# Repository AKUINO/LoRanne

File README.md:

# Long Range (LoRa) Radio Sensors for AKUINO
After connecting wired 17 sensors to a single AKUINO, we were convinced that wireless is very useful...

With the advent of LoRA transmission technology which ensures a really good indoor range, with the availability of ready to use modules like AdaFruit Feather M0 able to transmit data for years with simple batteries, we are convinced that a very performant solution can be created.
## Hardware

Transmitters (working on batteries, collecting and transmitting sensors data, sleeping most of the time) are explained further here: https://github.com/AKUINO/RadioSensor/tree/master/transmitter

Receiver(s) (powered, collecting transmitted data, archiving it locally, transmitting on Internet, never sleeping) is explained further here: https://github.com/AKUINO/RadioSensor/tree/master/receiver

General design considerations:

* Transmitters: Arduino MKR WAN 1300 https://store.arduino.cc/mkr-wan-1300 (was AdaFruit Feather M0: https://www.adafruit.com/product/3179 but AdaFruit products are rarely certified "CE")
* Receiver: for transmitters, we are also switching to an integrated "CE" marked product, M5STACK Code Module: https://m5stack.com/collections/m5-core
* 1-Wire sensors have the advantage of being self-identified, "hot-pluggable" and could be connected to one sensor node or another: https://www.maximintegrated.com/en/app-notes/index.mvp/id/4206
  * Serial adapter for 1-Wire gives better reliability than bit-banging (e.g. https://www.mikroe.com/uart-1-wire-click ) but requires 5V. As most 1-Wire devices are happy (but sometimes slower) at 3.3V, fewer devices not too far away will make bit-banging possible.
  * Thermocron (IButton: https://be.farnell.com/fr-BE/c/semiconducteurs-circuits-integres/memoires/accessoires-iboutons/iboutons ) can receive a "mission" and record temperature OFF-LINE for very long period of time: they can be used to ensure cold-chain continuity during transportation. They can even be programmed by a remote radio module: http://arduinofun.blogspot.com/2010/04/arduino-ibutton-data-logger-programmer.html . We have programmed data download and missioning of Thermocron by ELSA
  * Mains Switch: https://www.axiris.eu/en/index.php/1-wire/1-wire-mains-switch
* I2C sensors are often working at 3.3V and 5V. Short wires though (20 cm max: should be in the same box than the radio module)
  * I2C CO2+temperature+humidity: https://befr.rs-online.com/web/p/products/1720552/?grossPrice=Y&cm_mmc=BE-PLA-DS3A-_-google-_-PLA_BE_NL_Semiconductors-_-Sensor_Ics|Temperature_And_Humidity_Sensors-_-PRODUCT_GROUP&matchtype=&pla-544508151584&gclid=Cj0KCQiAzKnjBRDPARIsAKxfTRA_NGOGs_dE9fBuCA61ZyCIf1GovlkXcqFPyUBE3JYgCDP7rXKEHxUaAuaREALw_wcB&gclsrc=aw.ds
  * I2C Temperature and/or humidity: https://befr.rs-online.com/web/c/semiconductors/sensor-ics/temperature-sensors-humidity-sensors/?searchTerm=i2c%20sensor&applied-dimensions=4293448979,4294510394,4294490065,4294505396,4294510395,4294510203,4294356324,4294821500 and also https://www.tindie.com/products/akdracom/temperature-humidity-sensor-probe-precision-ic/
  * Grove Wiring standard is often used and is similar to QWIIC from Sparkfun: https://www.sparkfun.com/qwiic (Grove as a normal pitch connector, Sparkfun is smaller; Beware: AdaFruit standard is different!):
  1. Yellow - SCL
  1. White - SDA (Blue for QWIIC)
  1. Red - VCC on all Grove Connectors
  1. Black - GND on all Grove Connectors
  M5Stack Core is equipped with a Grove I2C connector.
* Lithium Battery: https://shop.mchobby.be/accu-et-regulateur/746-accu-lipo-37v-4400mah-3232100007468.html , https://be.farnell.com/fr-BE/mikroelektronika/mikroe-1120/batterie-lithium-polymer-3-7v/dp/2786900 , https://www.onlylipo.com/21-1s-37-volts-1-element
* Enclosures:
  * We selected KRADEX 64mm x 88mm x 42mm: https://www.tme.eu/fr/details/z-56jh-abs/boitiers-universels/kradex/z56jh-abs/ looking like CEL-MAR 1-Wire boxes that we also use.
  * 8 x 8cm, 5cm deep: many electrical junction boxes
  * 10 x 10cm, 6cm deep: http://be.farnell.com/fr-BE/fibox/pcm-95-60-g/coffret-boite-polycarbonate-gris/dp/2473443

## Software
* RadioHead libraries: http://www.airspayce.com/mikem/arduino/RadioHead/index.html Be sure to use the latest version (1.89)
  * for LoRa: http://www.airspayce.com/mikem/arduino/RadioHead/classRH__RF95.html

* 1-wire:
  * Host driver: https://www.maximintegrated.com/en/products/ibutton/software/1wire/wirekit.cfm
  * Recommended by Adafruit: https://www.pjrc.com/teensy/td_libs_OneWire.html
  * Slave device emulation library: https://github.com/orgua/OneWireHub (in case we want to connect to host through 1-wire)

* AdaFruit Feather M0, Arduino IDE SAMD support: https://learn.adafruit.com/adafruit-feather-m0-basic-proto/using-with-arduino-ide

## LoRa
* Allowed duty cycle and power in different 868MHz bands: https://www.disk91.com/2017/technology/internet-of-things-technology/all-what-you-need-to-know-about-regulation-on-rf-868mhz-for-lpwan/ From this document, the best local bandwidth could be 869,3 to 869,4 limited to 10mW but with no duty cycle constraint.
  * We measured 7 packets of 37 characters per seconds when testing this radio band.  
* 433 MHz may not be allowed in production within Europe: the project may have to be announced as "RFID" if we stick to those frequencies
  * In this band, we reached 540 meters in a corn field (emmiter and receiver at the corn height; single wire antenna)
* Calculator of Allowed duty cycle for different LoRa configurations: https://docs.google.com/spreadsheets/d/1COg2J1at6j8meehTtvfj5TIiM8pbj4SvKf7sa-Oq5fU/edit#gid=1628588258
## Sensors
Each node can receive many kind of sensors and its firmware can be adapted for each situation: the USB programming port of the node can be used to either change the firmware or to access a terminal console and change parameters.

An important information is battery voltage: its value will always be read and transmitted (register 1).

### I2C
I2C runs on 5V but also on 3.3V (not all sensors but most). Wires must be kept very short (20cm max, less is better).

The commands are different for each type of sensors: the bus cannot be really "auto discovered" like with 1-Wire (see below). The only possible thing is to associate I2C addresses with possible devices...

### 1-Wire
1-Wire ensures auto-configuration (devices can be "discovered" on the bus). Each 1-Wire device have a unique 64 bits address which can be auto-discovered by polling the 1-Wire bus (owdir on Linux, the equivalent will have to be programmed using libraries like https://www.pjrc.com/teensy/td_libs_OneWire.html ). The 8 first bits of this address indicates a generic device type which will have to be known by the firmware to adapt itself to the characteristics of each device type (e.g. number of values, polling protocol, parasitic powering...). The 8 last bits are a CRC8 checksum of the 7 previous bytes. It must be verified after each transmission (wire or radio) to ensure data integrity.

List of existing device types: http://owfs.org/index.php?page=family-code-list

The device types that we really need to support at first are:
* 26 for the DS2438 Battery Monitor (used as an ADC for various types of sensors like RH, CO2...)
* 28 for the DS18B20 Temperature Sensor; a library directly supporting this device seems to exist: https://github.com/milesburton/Arduino-Temperature-Control-Library This may be the best way to start supporting some sensors...
* 01 for the DS1990 simulated by RFID badge reader

A central directory of 1-Wire devices will be kept locally but also in the Receiver (and in ELSA application).

Every minutes or 5 (or any delay set in configuration), the node will transmit the raw data (no scaling) read for the different sensors. The allocation table will be transmitted every hour (or delay set in configuration) or on request by the central node (after detection of a checksum mismatch with the allocation table).

Data will be processed by the sensor node to transmit only specific JSON data values like "temperature" and not all registers of the device.

## Messages
* Encryption: http://www.airspayce.com/mikem/arduino/RadioHead/classRHEncryptedDriver.html#details
* Header with:
  * "FROM" (for sensors, the id of current node; for central node, id to distinguish the right central node)
	  * encoded on one byte
  * "TO" (for sensors, id of their central node; for central node, 255 for broadcast or id of a specific node to be queried)
	  * encoded on one byte
  * "ID", for a given "FROM"-"TO"-"FLAGS" combination, is a sequence ID of the message (overflow at 255): it allows the receiver to detect it has missed messages (and take action to correct this situation if needed).
  * "FLAGS" specifies the type of message: sensors data vs actuators (registers) setting; retransmission request (messages missed by receiver, the receiver signals which ID are missing); devices table to identify connected 1-Wire or I2C devices (from sensor node to central); relaying (MESH protocol, to be designed)
  * Sensors Data message: see below

## Sensors Data Messages
There are many encoding formats (see bottom of https://github.com/AKUINO/JBCDIC/blob/master/README.md ).

Please look at our proposal, the project AKUINO/JBCDIC: https://github.com/AKUINO/JBCDIC !

## Protocol
* A potential source of inspiration: https://github.com/fredilarsen/ModuleInterface/blob/master/documentation/Protocol.md
* A remote module (sensors) is sleeping most of the time (does not listen to radio) and awakens from time to time (around 3 minutes) to collect data and send it to the central module.
* A central module is listening all the time and sends actuators settings (or retransmission requests) only just after receiving sensors data from a remote module.
* The sender listen to the air and wait for silence (random delay) to avoid collision (this is done by the radio chip SX127x but needs to be configured. Looking at RadioHead library source code, it can be done: https://github.com/adafruit/RadioHead/blob/master/RH_RF95.h ). This is called LBT (Listen Before Talk).
* The message is sent using RadioHead library (encrypted but no ACK required).
* For remote module, the sender keeps listening for eventual input messages from the destination (actuators settings, sensors data retransmission requests) during a short period of time.
* If a remote module notices that some actuators settings are missing, it requests their retransmission.
* Sensor nodes send their 1-Wire / I2C Allocation table either periodically (about an hour), either when some connection changes is detected or whenever a request for it is received from the central node
* Retransmission request: timestamp + pairs of bytes for each ID intervals ("begin ID"-"end ID") that needs to be (re)transmitted. Overflow may occur (increment of 255 is 0) and "end ID" can be lower than "begin ID".
* Retransmission: message with exactly the same Header (TO, FROM, ID, FLAGS) and Payload than the one transmitted before

All nodes will be responsible to keep a buffer of the last messages (254 last messages for sensors and 254 last messages for actuators) they sent.

Redundancy of central module is possible: the two modules then share the same ID. A central module may not have received a package and therefore ask to retransmit a message well received by the other module: redundant transmissions are therefore discarded based on ID+timestamp.

## Configuration
We will use a serial terminal (USB) to set the configuration parameters (ANSI character codes for colors). We have the necessary code in C++ for PIC32. The configuration will have to assign a key (0 to 31) to the physically connected ports:
* Digital inputs: for a 1st version, we will statically map some GPIO as 0/1 ports
* Analog inputs (12 bits): for a 1st version, we will statically map some ADC inputs including at least the battery level and 2 ADC lines
* Digital outputs (PWM, pull-up, delays) to be SET (based on messages received from central): for a 1st version, we will statically map some PWM lines with basic local configuration attributes.
* 1-Wire (multiple sensors: 1-Wire addresses AUTOMATICALLY mapped to different keys but a selection of registries may have to be done based on the device type. ABANDONED for now due to lack of 5V...)
* Serial link (not for a 1st version except if a precise need arise)
* Campbell SDI (not for a 1st version except if a precise need arise)
* I2C device initialization command and register read: this is not well standardized but we will try to orthogonalize the possibilities.
A basic polling cycle (e.g. 3 minutes) has to be set. Each key can be obtained either at each poll or at a configured multiple.

## References
* The Ten Commandments of Wireless Communications: http://www.bb-elec.com/Learning-Center/All-White-Papers/Wireless-Cellular/10-Commandments-of-Wireless-Communications/10_Commandments_Wireless_WP033_R2-1112.pdf
* Detailed RadioHead interface: https://github.com/adafruit/RadioHead/blob/master/RH_RF95.h
* The standard pinout of Feather M0 is: https://cdn-learn.adafruit.com/assets/assets/000/046/244/original/adafruit_products_Feather_M0_Basic_Proto_v2.2-1.png?1504885373
* Similar project but for very long range: http://cpham.perso.univ-pau.fr/LORA/WAZIUP/FAQ.pdf
  * http://cpham.perso.univ-pau.fr/LORA/WAZIUP/SUTS-demo-slides.pdf
* CayenneLPP: https://mydevices.com/cayenne/docs/lora/#lora-cayenne-low-power-payload
* PJON, an alternative transmission protocol: https://github.com/fredilarsen/ModuleInterface/blob/master/documentation/Protocol.md
* PlugAndPlay mechanism for small IoT networks using "off the shelf" sensors: http://pitkaaho.net/varasto/2013_IJSNet.pdf
* MainFlux does not seems to be locking anything (to double check!) and is involved in FIWARE and is very near of a good gateway for ELSA: https://www.mainflux.com/index.html
* LORD-MicroStrain is locking by the hardware : https://github.com/LORD-MicroStrain/
* UbiWorX is locking by the platform: https://ubiworx.com/documentation/introduction/introduction.html
* W3C API: https://w3c.github.io/sensors/

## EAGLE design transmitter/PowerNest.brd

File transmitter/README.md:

# TRANSMITTER
In a "star" network there are modules collecting data in different places (transmitters) and one or two "data sinks" (receivers, gateways) that route the data to the data management application.

The transmitters must be as autonomous as possible (minimal configuration, automatic adaptation to new sensors put in place, agnostic about the data: it will be managed by the application, not the transmitter).

They include:
* power management: sensors are powered only when needed, battery power is saved as much as possible
* radio bandwidth management: radio transmission is minimized and assumed "dangerous": if it fails, data is kept up to the moment transmission can resume.

The configuration needed is minimal:
* a Network ID is provided once for all and needs a special boot-up sequence and password to be changed.
* a Network access key and a unique Module ID must be set. They remain normally unchanged. Another password protects those parameters.

The peripherals are automatically detected (1-Wire, I2C). Some may have to be configured (Analog or serial inputs). This is done through a wizard (sequence of questions with current answers provided by defaults).

Radio messages are buffered and exchanged in compressed URL format (see project [JBCDIC](https://github.com/AKUINO/JBCDIC/blob/master/README.md), aimed at compressiong JSON, used to compress URLs).

The transmitter is currently based on the Adafruit Feather M0 with a LoRa transmitter (https://www.adafruit.com/product/3178) but next version will be based on Arduino MKR WAN 1300. We add an underlying board to ease connections to sensors and to selectively power them. The following table explains the pinout:

Connector|Code|Data Pin|Power Activation Pin|Remark
---------|----|--------|--------------------|------
J1-1|g|||GND
J1-2|T|TX (15)|A3 (8)|Serial TX, 10k pull-up
J1-3|R|RX (14)||Serial RX
J1-4|v||A3 (8)|Switched and limited Vcc (see below)
J1-5|g|||GND
J1-6|C|SCL (18)|D11 (23)|I2C clock, 5k pull-up
J1-7|D|SDA (17)|D11 (23)|I2C data, 5k pull-up
J1-8|v||D11 (23)|Switched and limited Vcc (see below)
J1-9|g|||GND
J1-10|O|D13 (25)||LED: Switched Vcc but limited (see below) and 100 ohm
J1-11|I|A0 (5)||Button switch; Analog input protected and filtered for 50Hz
J1-12|v|||Unswitched Vcc limited by 100 ohm
J2-1|g|||GND
J2-2|1|A1 (6)||Analog input protected and filtered for 50Hz
J2-3|v||A4 (9)|Switched and limited Vcc (see below)
J2-4|g|||GND
J2-5|2|A2 (7)||Analog input protected and filtered for 50Hz
J2-6|v||A5 (10)|Switched and limited Vcc (see below)
J2-7|g|||GND
J2-8|W|D5 (19)|D12 (24)|1-Wire bus, 5k pull-up
J2-9|v||D12 (24)|Switched and limited Vcc (see below)
J2-10|10|D10 (22)||Switched and limited Vcc (see below)
J2-11|6|D6 (20)||Switched and limited Vcc (see below)
J2-12|v7||D12 (24)|Switched 7 volts to power RFID/NFC reader (small DC/DC converter from D12)

Distributed power is switched by a TBD62783APG DMOS transistor array (clamping diode included), limited by a 300ma temporary fuse, a 18µH inductance and sustained by a 3µF capacitor.

Detailed Eagle schema and board definition are in this directory.

## Data transmitted

Data is encoded as an URL using JBCDIC ( https://github.com/AKUINO/JBCDIC ). A message is made of only one (for now) session of measures up to the LoRa maximum size (53 bytes in our case).

One measurements session is a URL (in the future: a JSON object) with the following properties:

Property|Connection|Pin|Description
--------|----------|---|-----------
H0|||Seconds ellapsed since module startup. H0 is replaced by H with the correct time by the receiver before resending to the Web application
H|||Seconds since 01/01/2019 (if time was broadcasted by receiver ("data sink") and synchronized with transmitter)
N|||Network Identification number: Not transmitted but added by the receiver before resending to the Web application
M|||Radio Module Identification number: Not transmitted but added by the receiver before resending to the Web application
R|||RSSI for this message: Not transmitted but added by the receiver before resending to the Web application
A0|J1-11|A0|Button pressed? Not transmitted if 0
A1|J2-2|A1|Analog input 1. Not transmitted if 0
A2|J2-5|A2|Analog input 2. Not transmitted if 0
B||A6|Battery voltage
B5||A7|USB voltage (if present). Usually 5 volts if connected
B9|||Last RSSI of messages broadcasted by Receiver (decimal)
C|J1-3|RX|Serial data received (string)
Dnnn|J2-8|D5|Value (or array of values or object with different properties) obtained from 1-Wire device at address "nnn..." (decimal)
G|J2-8|D5|Last badge read by RFID reader (encoded in decimal). Not transmitted if none
G0|J1-10|D13|Button LED on? Not transmitted if not
G1|J2-10|D10|Yellow LED of RFID reader is on? Not transmitted if not
G2|J2-11|D6|Red LED of RFID reader is on? Not transmitted if not
Innn|J1-7|I2C|Value (or array of values or object with different properties) obtained from I2C device at address "nnn" (decimal)

### Data transmission example

Before compression to 4 bits per character:
`{H0+3602A0+1B+3-12B9-78D159300978176+27-2I68[+27-5+40-5]}`
which means:
* `H0+3602` : 3602 seconds elapsed since starting the radio module
* `A0+1` : Button is pressed
* `B+3-12` : Battery is 3.12V
* `B9-78` : Last RSSI was -78 (in decimal)
* `D159300978176+27-2` : the temperature sensor address is 0x2517140600 (not including the leading 0x28 indicating its type and the trailing byte providing an CRC) and its temperature is 27.2°C
* `I68[+27-5+40-5]` : the I2C device at address 0x44 (usually an SHT31 sensor) provides two values: 27.5°C and 40.5% rH

The receiver will receive this data and retransmit it to the Internet application in standard JSON and adding network/module identification:

~~~~
  [ { H:(date/time in seconds elapsed since 1/1/1970 as in UNIX),
     N:1,   (network id)
     M:3,   (module id)
     R:-77,   (RSSI of transmitted message)
     A0:1,     
     B:3.12,    
     B9:-78,    
     D159300978176:27.2,    
     I68:[27.5,40.5]   
    } 
  ]
~~~~

## Software
* Radiohead library for encrypted Lora transmissions
* Protohead for simultaneous execution of data collection and radio transmission
* Periodical wake-ups for collection of sensors values and LoRa transmission (Listen before talk, random delay)
* USB Serial port for the configuration wizard
* JBCDIC for data compression
* FIFO Round Robin Buffer for unacknowledged transmitted data
* Watchdog on button for immediate wakeup, NFC/RFID scan and immediate transmission of status data (including the "button pressed" indication)

## Extensions
* To control equipement in adverse electrical environments, insulation of 1-Wire bus may be useful:  http://www.ti.com/lit/ds/symlink/iso1540.pdf

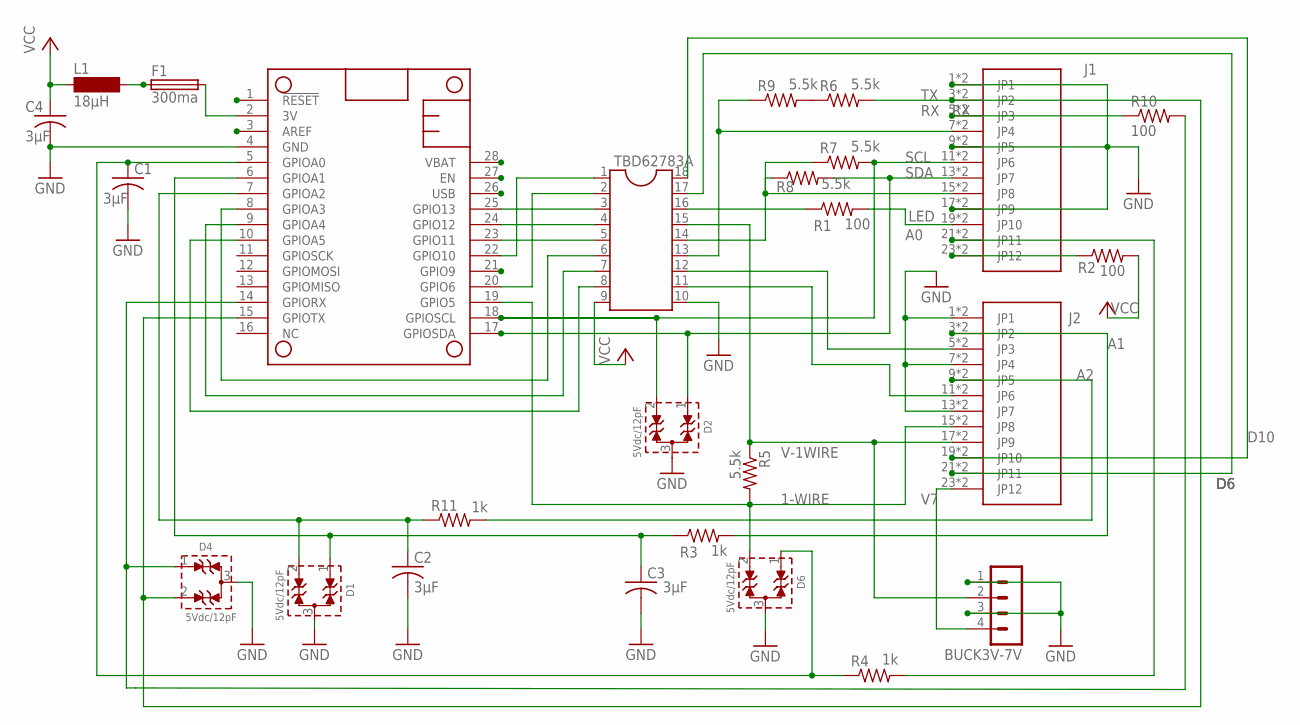
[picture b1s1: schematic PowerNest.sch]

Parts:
BUCK3V-7V: MA04-1
C1, C2, C3, C4: 3µF; C1206K
D1, D2, D4, D6: 5Vdc/12pF; WE-TVS_SOT23-3L
F1: 300ma; TE5
FEATHER: FEATHERWING_NODIM; FEATHERWING_DIM
J1, J2: MC000008B; CONNECTED
L1: 18µH; BS11
R1, R2, R10: 100; R1206
R3, R4, R11: 1k; R1206
R5, R6, R7, R8, R9: 5.5k; R1206
TBD62783A: DIL18S; SOCKET-18

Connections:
1-WIRE: D6.2 (I/O2), FEATHER.19 (GPIO5), J2.15 (JP8), J2.16 (JP8), R5.2
3V: F1.2, FEATHER.2 (3V)
A0: J1.21 (JP11), J1.22 (JP11), R4.2
A1: J2.3 (JP2), J2.4 (JP2), R3.2
A2: J2.9 (JP5), J2.10 (JP5), R11.2
D6: J2.21 (JP11), J2.22 (JP11), TBD62783A.17
D10: J2.19 (JP10), J2.20 (JP10), TBD62783A.18
GND: BUCK3V-7V.1, BUCK3V-7V.3, C1.2, C2.2, C3.2, C4.2, D1.3 (GND), D2.3 (GND), D4.3 (GND), D6.3 (GND), FEATHER.4 (GND), J1.1 (JP1), J1.2 (JP1), J1.9 (JP5), J1.10 (JP5), J1.17 (JP9), J1.18 (JP9), J2.1 (JP1), J2.2 (JP1), J2.7 (JP4), J2.8 (JP4), J2.13 (JP7), J2.14 (JP7), TBD62783A.10
LED: J1.19 (JP10), J1.20 (JP10), R1.2
unnamed: FEATHER.25 (GPIO13), TBD62783A.3
unnamed: FEATHER.8 (GPIOA3), TBD62783A.6
unnamed: FEATHER.24 (GPIO12), TBD62783A.4
unnamed: FEATHER.23 (GPIO11), TBD62783A.5
unnamed: FEATHER.9 (GPIOA4), TBD62783A.7
unnamed: FEATHER.10 (GPIOA5), TBD62783A.8
unnamed: F1.1, L1.2
unnamed: J1.15 (JP8), J1.16 (JP8), R7.1, R8.1, TBD62783A.14
unnamed: J1.7 (JP4), J1.8 (JP4), R9.1, TBD62783A.13
unnamed: C3.1, D1.1 (I/O1), FEATHER.6 (GPIOA1), R3.1
unnamed: C2.1, D1.2 (I/O2), FEATHER.7 (GPIOA2), R11.1
unnamed: R6.1, R9.2
unnamed: J2.5 (JP3), J2.6 (JP3), TBD62783A.12
unnamed: J2.11 (JP6), J2.12 (JP6), TBD62783A.11
unnamed: D4.1 (I/O1), FEATHER.14 (GPIORX), R10.2
unnamed: R1.1, TBD62783A.16
unnamed: J1.23 (JP12), J1.24 (JP12), R2.1
unnamed: C1.1, D6.1 (I/O1), FEATHER.5 (GPIOA0), R4.1
unnamed: FEATHER.22 (GPIO10), TBD62783A.1
unnamed: FEATHER.20 (GPIO6), TBD62783A.2
RX: J1.5 (JP3), J1.6 (JP3), R10.1
SCL: D2.2 (I/O2), FEATHER.18 (GPIOSCL), J1.11 (JP6), J1.12 (JP6), R7.2
SDA: D2.1 (I/O1), FEATHER.17 (GPIOSDA), J1.13 (JP7), J1.14 (JP7), R8.2
TX: D4.2 (I/O2), FEATHER.15 (GPIOTX), J1.3 (JP2), J1.4 (JP2), R6.2
USB: FEATHER.26 (USB)
V7: BUCK3V-7V.4, J2.23 (JP12), J2.24 (JP12)
V-1WIRE: BUCK3V-7V.2, J2.17 (JP9), J2.18 (JP9), R5.1, TBD62783A.15
VBAT: FEATHER.28 (VBAT)
VCC: C4.1, L1.1, R2.2, TBD62783A.9

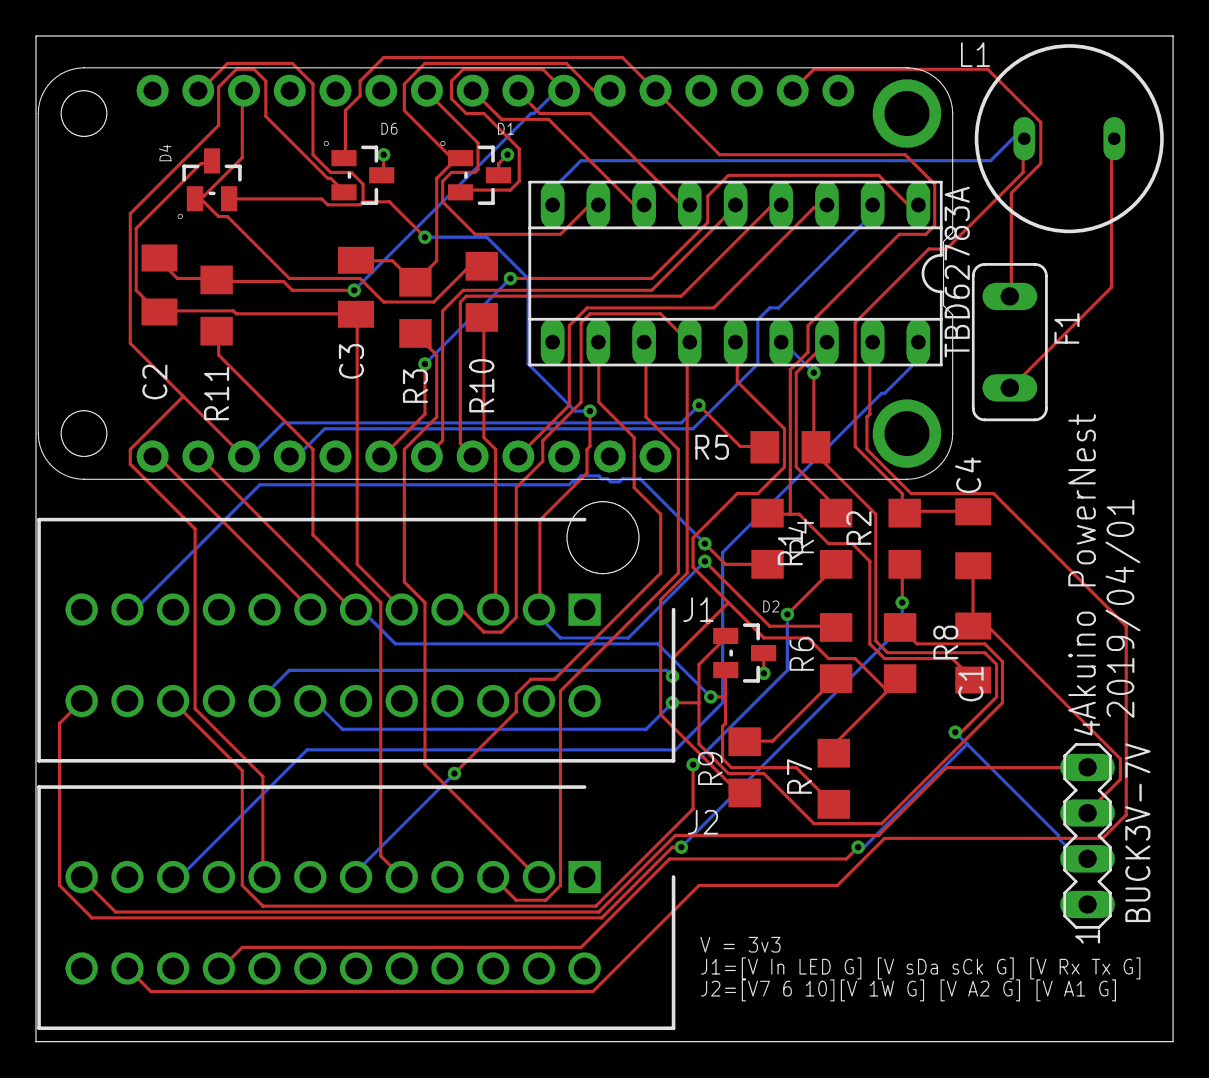
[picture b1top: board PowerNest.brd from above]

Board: 2 copper layers, 63.2 x 55.9 mm, 26 parts (0 on the bottom side), 36 nets.

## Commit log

2018-06-25 radio packet representation
2018-06-26 modification protocole
2018-06-27 Changement sur la sécurité des transmissions
    Autres à venir cet aprèsm
2018-06-27 Protocol improved...
2018-08-25 Update README.md
    Add description of 1-Wire bus integration
2018-09-12 1-Wire connexion to host?
2018-10-17 helloworld lorasensor
2019-01-18 Update README.md
    Add duty cycle info...
2019-02-28 1-Wire is 3.3V tolerant in most cases
2019-03-25 Restructure...
2019-04-01 Eagle files for the power control board
2019-05-20 Apport de Badr
2019-05-20 ESP32 connections
2019-05-20 Relay1 inversion!
2019-05-29 Salon du Fromage
2019-06-03 Derniere modif
2019-06-24 PDF for schema
2019-07-12 add our FIFO library
2019-07-23 alpha
2019-07-23 cleaning code
2019-07-23 alpha transmitter
2019-07-25 finalisation envoi des données sur le serveur
2019-07-26 ajout du compressage decompressage dans le transmitter
2019-07-30 UBCDIC plutot que JBCDIC!
2019-08-01 code review
2019-08-01 ACK is enough to confirm receive
2019-08-02 Code review (bis)
2019-08-14 Derniere modif de Romain

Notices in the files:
parts and their libraries:
EMCComponents: Copyright: Würth Elektronik
